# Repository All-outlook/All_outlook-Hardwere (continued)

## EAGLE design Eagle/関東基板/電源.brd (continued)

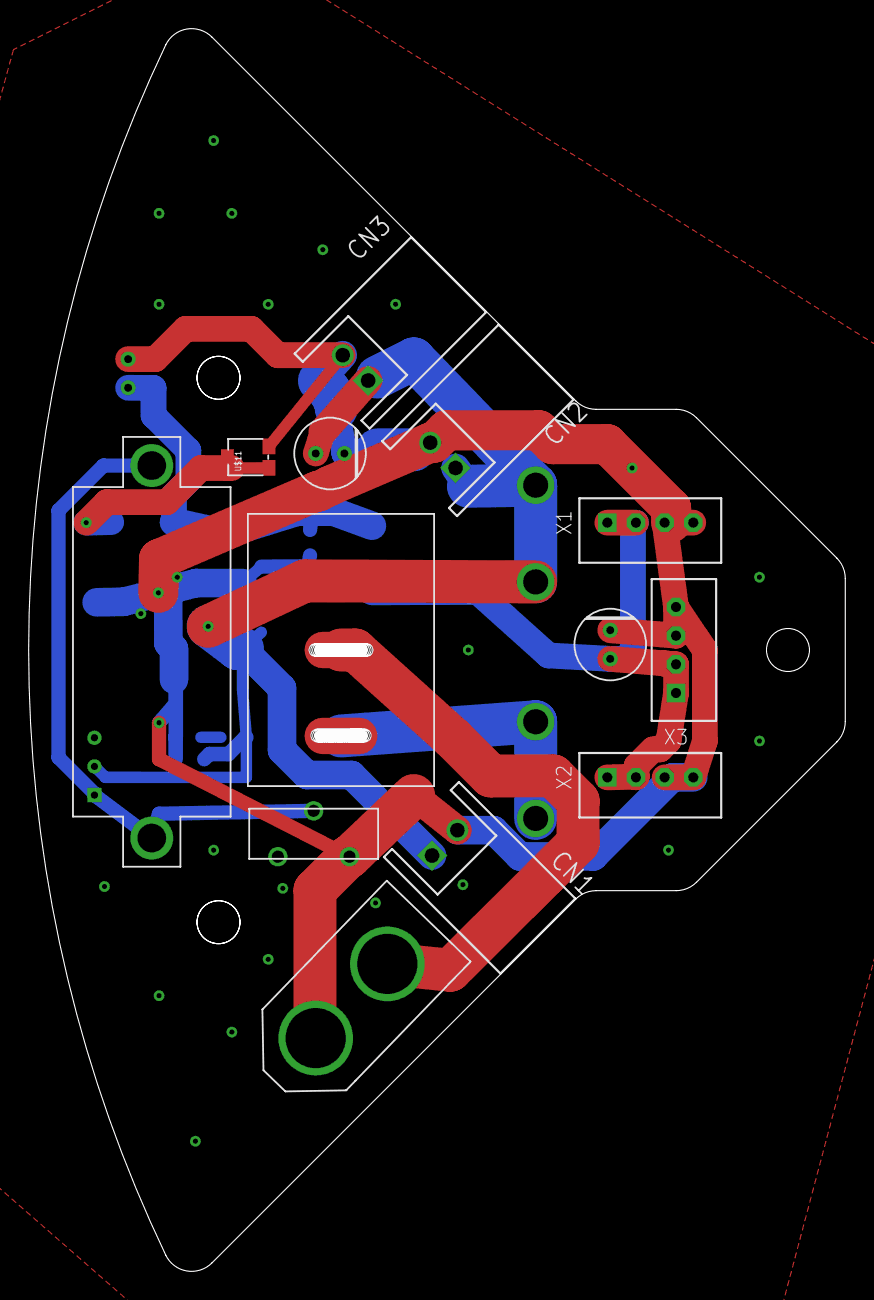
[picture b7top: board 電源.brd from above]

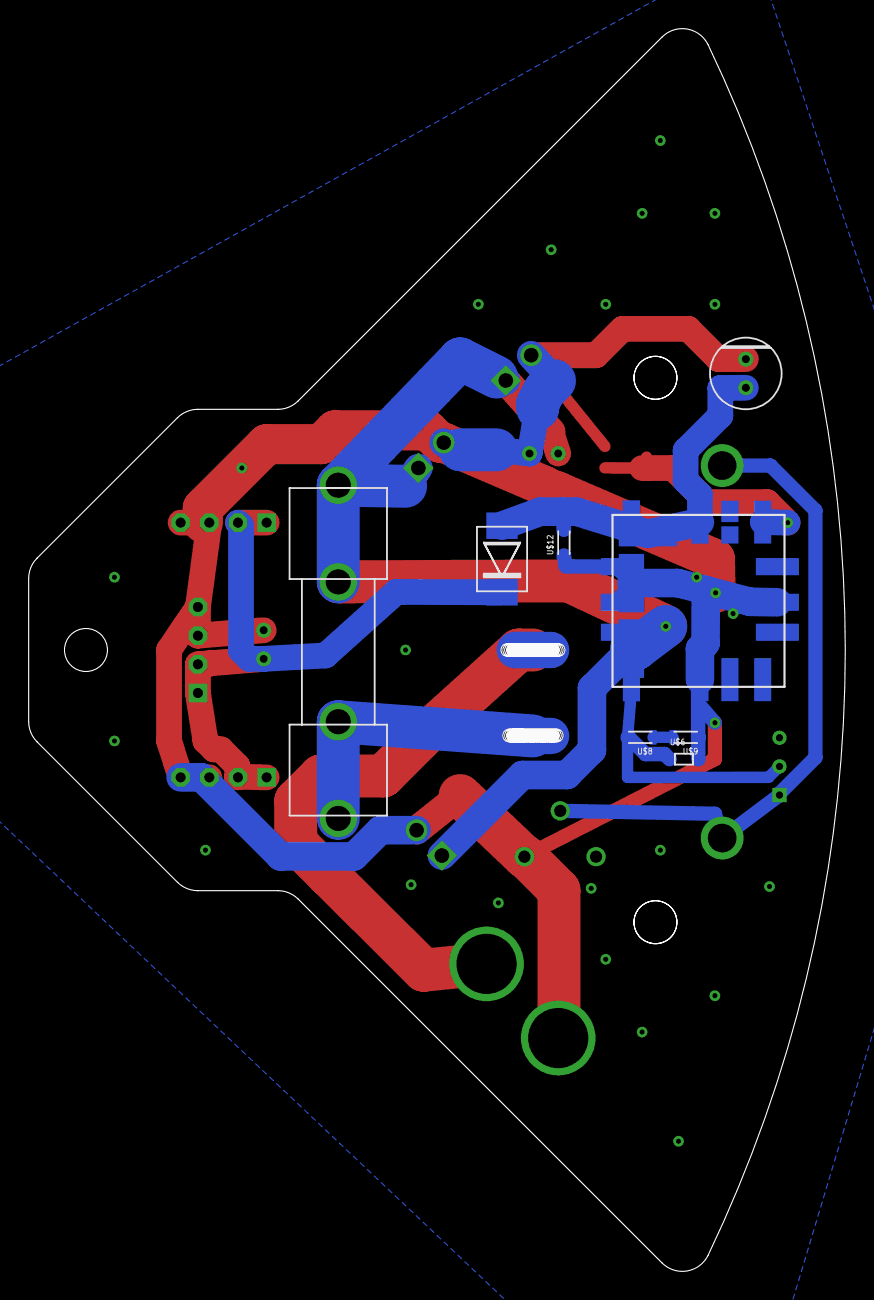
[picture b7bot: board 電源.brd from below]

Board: 2 copper layers, 57.0 x 86.7 mm, 21 parts (8 on the bottom side), 9 nets.
